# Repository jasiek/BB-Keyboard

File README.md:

BB-Keyboard
=================

> A complete module that acts as a SPI/I2C keyboard, which uses OEM surplus Blackberry keyboards and micro switches.

### Bill of materials

#### [Blackberry Q5 Keyboard](http://www.aliexpress.com/item/New-Original-For-Blackberry-Q5-Housing-Keypad-Keyboard-Qwerty-Black-Or-White-Free-Shipping/32337504795.html) ($3)

#### [3x4x2mm SMD Tactile Switches](http://www.aliexpress.com/item/200PCS-3-4-2MM-3X4X2mm-SMD-Tact-2P-miniature-micro-switch-button-switch-new-Original-Push/32595638808.html) ($4)

#### TBD... looking for a keboard/matrix scanner.

|Chip|Description|Package|Price ($)|OK?|
|---|---|---|---|---|
|LM8330|I2C Keypad Controller|DSBGA|1.70|:x: (2x2mm BGA)|
|MAX7360|I²C-Interfaced Key-Switch Controller|QFN|4.65|:ok:, expensive|
|ADP5586|Keypad Decoder and I/O Exp|BGA|2.08|:x: (1.6x1.6 BGA)|
|BU1852GUW|Key encoder|BGA|2.07|:x: (4mm BGA)|
|TCA8418|I2C Controlled Keypad Scan IC|QFN|3.15|:ok:|

This is a work-in-progress.

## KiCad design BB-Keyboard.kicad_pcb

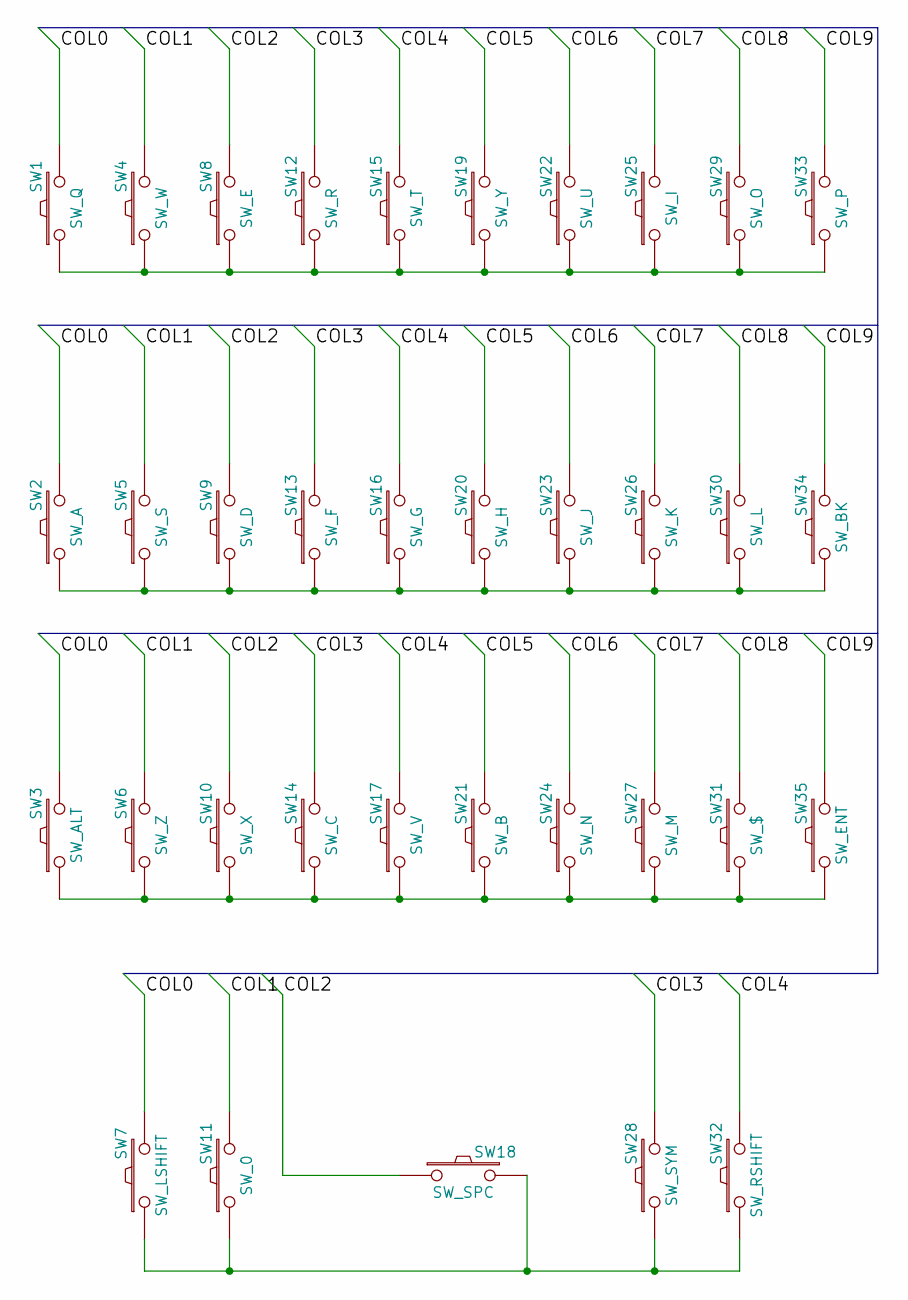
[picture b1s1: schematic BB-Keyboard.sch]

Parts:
SW1: SW_Q
SW2: SW_A
SW3: SW_ALT
SW4: SW_W
SW5: SW_S
SW6: SW_Z
SW7: SW_LSHIFT
SW8: SW_E
SW9: SW_D
SW10: SW_X
SW11: SW_0
SW12: SW_R
SW13: SW_F
SW14: SW_C
SW15: SW_T
SW16: SW_G
SW17: SW_V
SW18: SW_SPC
SW19: SW_Y
SW20: SW_H
SW21: SW_B
SW22: SW_U
SW23: SW_J
SW24: SW_N
SW25: SW_I
SW26: SW_K
SW27: SW_M
SW28: SW_SYM
SW29: SW_O
SW30: SW_L
SW31: SW_$
SW32: SW_RSHIFT
SW33: SW_P
SW34: SW_BK
SW35: SW_ENT

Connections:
/COL0: SW1.2, SW2.2, SW3.2, SW7.2; also elsewhere on the board
/COL1: SW4.2, SW5.2, SW6.2, SW11.2; also elsewhere on the board
/COL2: SW8.2, SW9.2, SW10.2, SW18.1; also elsewhere on the board
/COL3: SW12.2, SW13.2, SW14.2, SW28.2; also elsewhere on the board
/COL4: SW15.2, SW16.2, SW17.2, SW32.2; also elsewhere on the board
/COL5: SW19.2, SW20.2, SW21.2; also elsewhere on the board
/COL6: SW22.2, SW23.2, SW24.2; also elsewhere on the board
/COL7: SW25.2, SW26.2, SW27.2; also elsewhere on the board
/COL8: SW29.2, SW30.2, SW31.2; also elsewhere on the board
/COL9: SW33.2, SW34.2, SW35.2; also elsewhere on the board
/ROW0: SW1.1, SW4.1, SW8.1, SW12.1, SW15.1, SW19.1, SW22.1, SW25.1, SW29.1, SW33.1; also elsewhere on the board
/ROW1: SW2.1, SW5.1, SW9.1, SW13.1, SW16.1, SW20.1, SW23.1, SW26.1, SW30.1, SW34.1; also elsewhere on the board
/ROW2: SW3.1, SW6.1, SW10.1, SW14.1, SW17.1, SW21.1, SW24.1, SW27.1, SW31.1, SW35.1; also elsewhere on the board
/ROW3: SW7.1, SW11.1, SW18.2, SW28.1, SW32.1; also elsewhere on the board

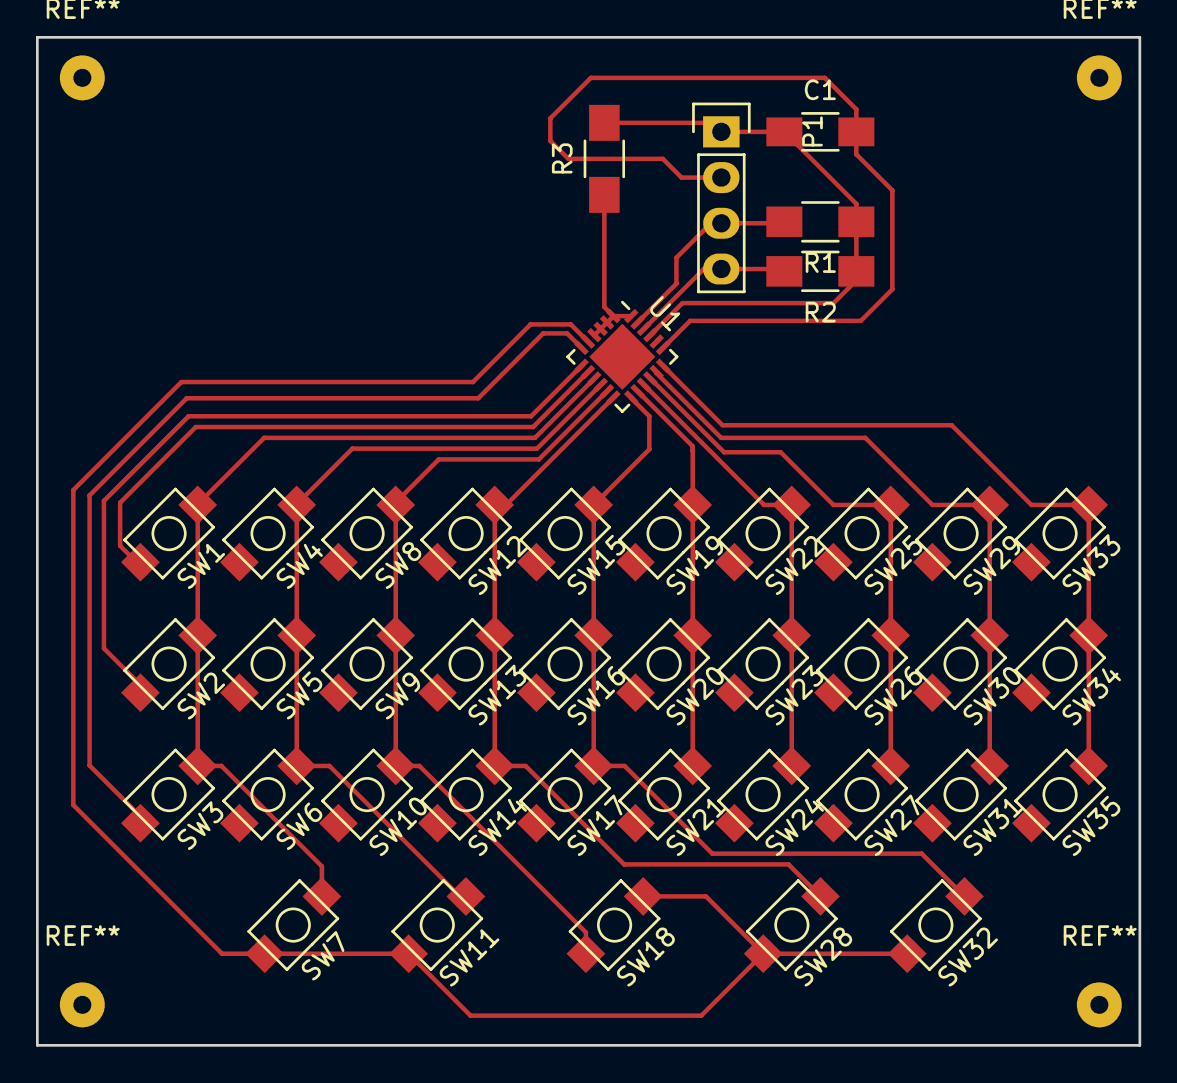
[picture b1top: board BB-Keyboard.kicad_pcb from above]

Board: 2 copper layers, 61.2 x 56.0 mm, 41 parts (0 on the bottom side), 19 nets.

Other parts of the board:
C1: C_Small; C_1206_HandSoldering
P1: CONN_01X04; Socket_Strip_Straight_1x04
R1, R2: 4.7k; R_1206_HandSoldering
R3: 10k; R_1206_HandSoldering
U1: TCA8418; TCA8418RTWR

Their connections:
+3V3: C1.1, P1.1, R1.1, R2.1, R3.2, U1.21
/COL0: U1.9; also elsewhere on the board
/COL1: U1.10; also elsewhere on the board
/COL2: U1.11; also elsewhere on the board
/COL3: U1.12; also elsewhere on the board
/COL4: U1.13; also elsewhere on the board
/COL5: U1.14; also elsewhere on the board
/COL6: U1.15; also elsewhere on the board
/COL7: U1.16; also elsewhere on the board
/COL8: U1.17; also elsewhere on the board
/COL9: U1.18; also elsewhere on the board
/ROW0: U1.8; also elsewhere on the board
/ROW1: U1.7; also elsewhere on the board
/ROW2: U1.6; also elsewhere on the board
/ROW3: U1.5; also elsewhere on the board
GND: C1.2, P1.2, U1.19
unnamed: R3.1, U1.1, U1.2, U1.3, U1.4, U1.20, U1.24
SCL: P1.3, R1.2, U1.23
SDA: P1.4, R2.2, U1.22

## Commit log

2016-05-07 Initial commit.
2016-05-07 Some pictures.
2016-05-07 Updated readme.
2016-05-08 Buses, labels, et al.
2016-07-02 More labels and buses.
2016-07-02 Created a schematic symbol for TCA8418.
2016-07-02 Finished schematic.
2016-07-02 WIP, component outline changed, but not reflected on PCB.
2016-07-04 Aligned everything, but the alignment isn't right at all. Needs to be wider.
